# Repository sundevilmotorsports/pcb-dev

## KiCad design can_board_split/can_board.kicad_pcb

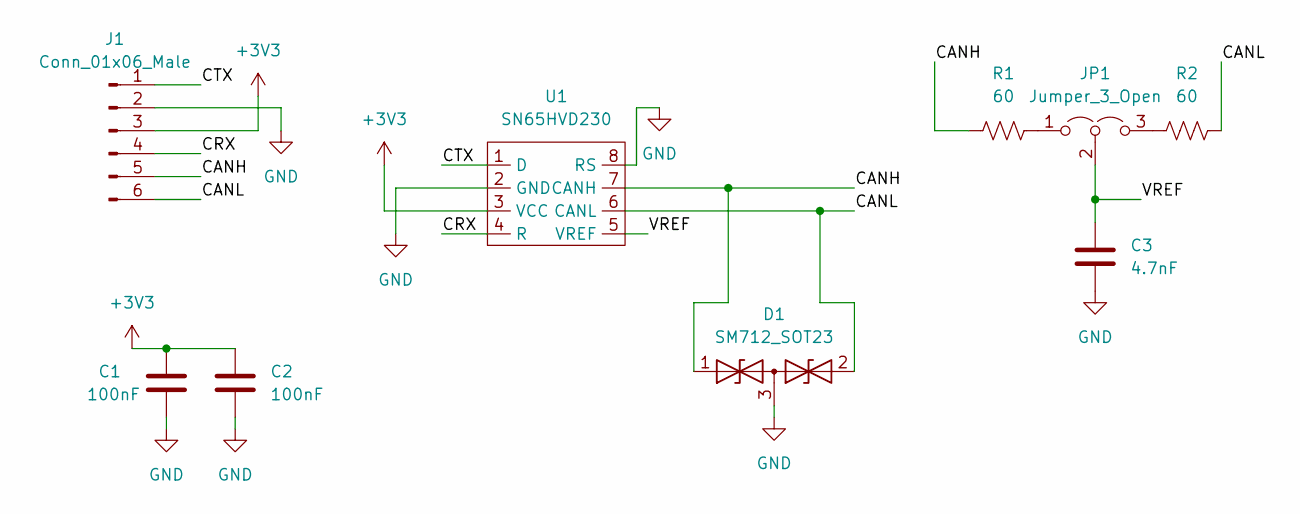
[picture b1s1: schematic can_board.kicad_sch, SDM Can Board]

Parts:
C1, C2: 100nF; CP_EIA-1608-08_AVX-J
C3: 4.7nF; CP_EIA-1608-08_AVX-J
D1: SM712_SOT23; SOT-23
J1: Conn_01x06_Male; PinHeader_1x06_P2.54mm_Vertical
JP1: Jumper_3_Open; PinHeader_1x03_P2.54mm_Vertical
R1, R2: 60; R_0603_1608Metric
U1: SN65HVD230; SOIC-8_3.9x4.9mm_P1.27mm

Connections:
+3V3: C1.1, C2.1, J1.3, U1.3 (VCC)
/CANH: D1.1 (A1), J1.5, R1.1, U1.7 (CANH)
/CANL: D1.2 (A2), J1.6, R2.2, U1.6 (CANL)
/CRX: J1.4, U1.4 (R)
/CTX: J1.1, U1.1 (D)
/VREF: C3.1, JP1.2 (C), U1.5 (VREF)
GND: C1.2, C2.2, C3.2, D1.3 (common), J1.2, U1.2 (GND), U1.8 (RS)
unnamed: JP1.1 (A), R1.2
unnamed: JP1.3 (B), R2.1

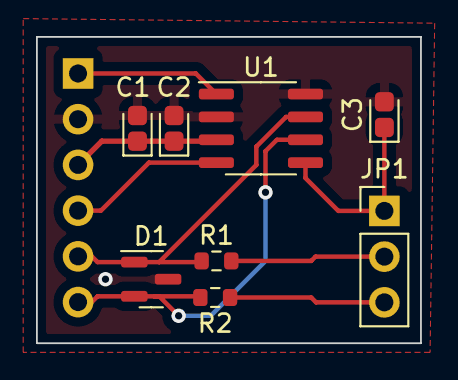
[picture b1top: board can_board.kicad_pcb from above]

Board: 2 copper layers, 21.3 x 17.0 mm, 9 parts (1 on the bottom side), 9 nets.

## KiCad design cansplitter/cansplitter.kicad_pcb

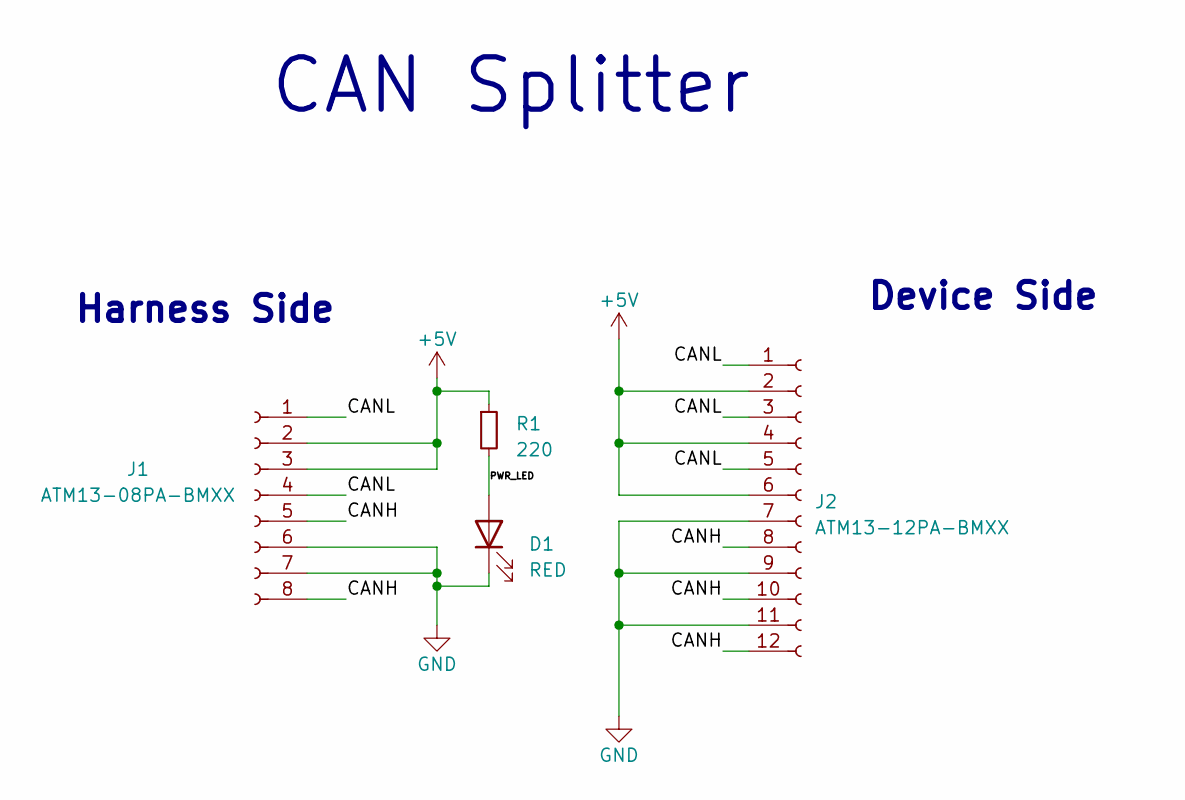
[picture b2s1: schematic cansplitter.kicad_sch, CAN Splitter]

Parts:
D1: RED; LED_1206_3216Metric
J1: ATM13-08PA-BMXX
J2: ATM13-12PA-BMXX
R1: 220; R_1206_3216Metric

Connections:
+5V: J1.2, J1.3, J2.2, J2.4, J2.6, R1.1
/CANH: J1.5, J1.8, J2.8, J2.10, J2.12
/CANL: J1.1, J1.4, J2.1, J2.3, J2.5
/PWR_LED: D1.2 (A), R1.2
GND: D1.1 (K), J1.6, J1.7, J2.7, J2.9, J2.11

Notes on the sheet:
Harness Side
Device Side
CAN Splitter

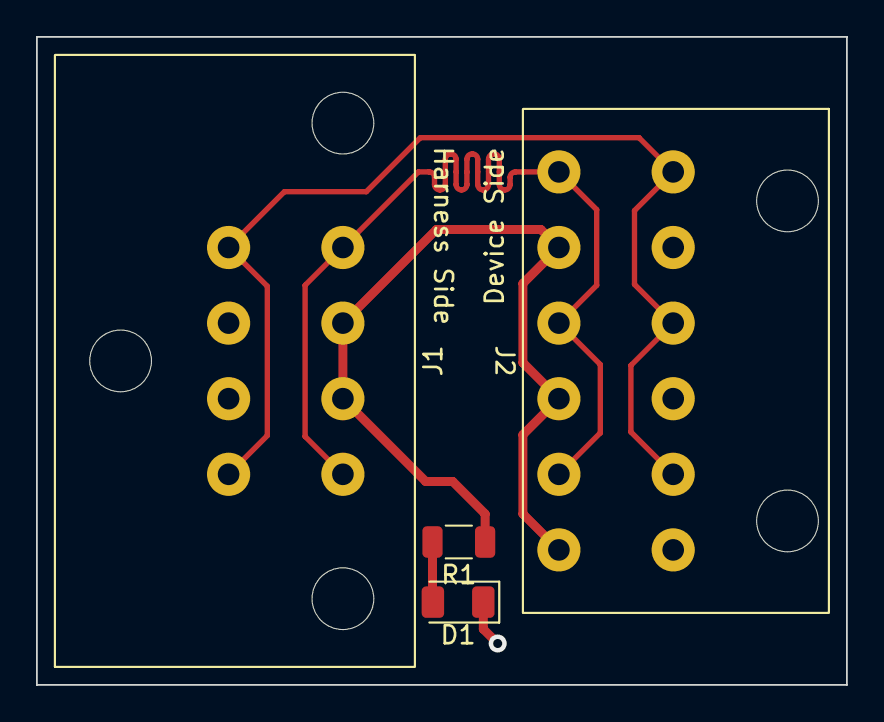
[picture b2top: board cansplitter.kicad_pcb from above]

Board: 2 copper layers, 45.0 x 36.0 mm, 4 parts (0 on the bottom side), 5 nets.

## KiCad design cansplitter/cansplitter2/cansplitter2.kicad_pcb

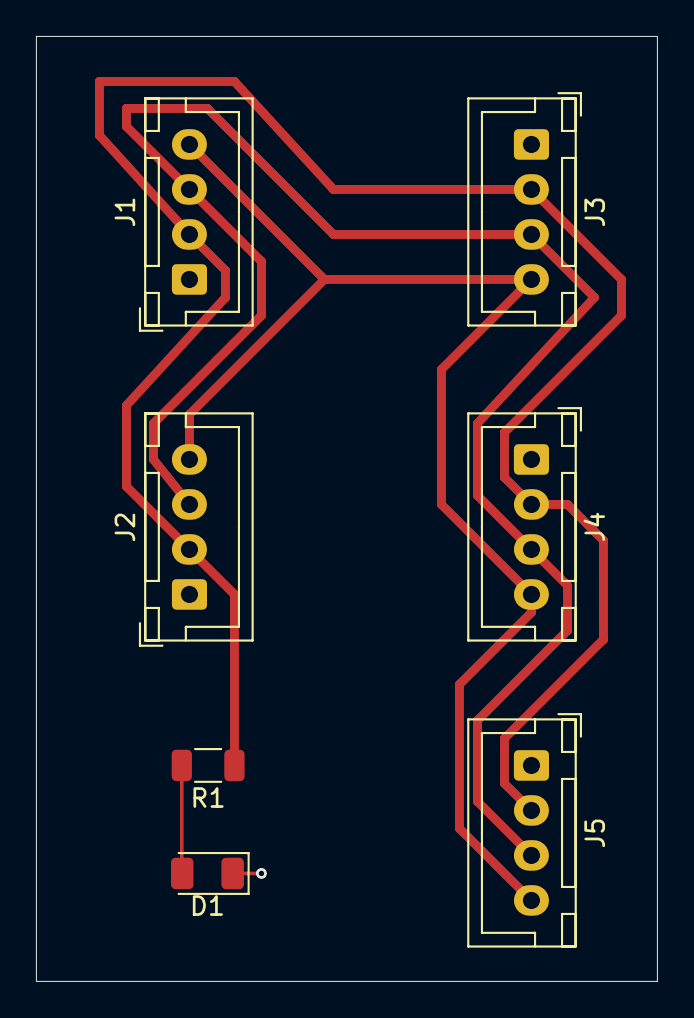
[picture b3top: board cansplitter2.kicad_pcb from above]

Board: 2 copper layers, 34.5 x 52.5 mm, 7 parts (0 on the bottom side), 5 nets.

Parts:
D1: RED; LED_1206_3216Metric
J1, J2, J3, J4, J5: JST-XH 1x4; JST_XH_B4B-XH-A_1x04_P2.50mm_Vertical
R1: 220; R_1206_3216Metric

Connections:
+5V: J1.2, J2.2, J3.2, J4.2, J5.2, R1.1
/CANH: J1.4, J2.4, J3.4, J4.4, J5.4
/CANL: J1.3, J2.3, J3.3, J4.3, J5.3
/PWR_LED: D1.2 (A), R1.2
GND: D1.1 (K), J1.1, J2.1, J3.1, J4.1, J5.1

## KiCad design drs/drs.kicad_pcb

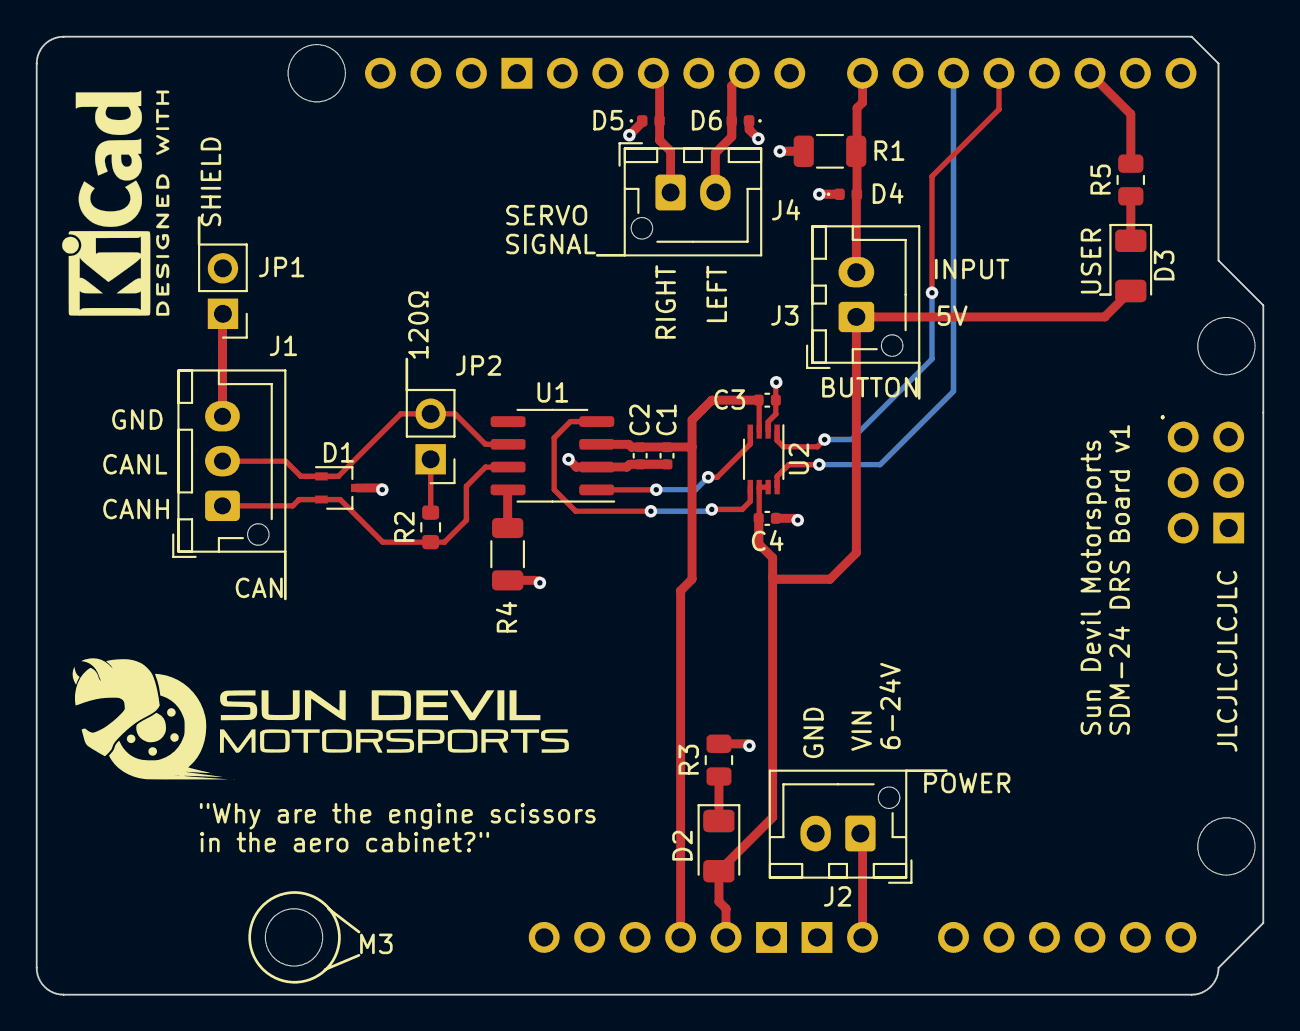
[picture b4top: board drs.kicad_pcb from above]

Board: 2 copper layers, 68.5 x 53.5 mm, 24 parts (0 on the bottom side), 19 nets.

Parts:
A1: Arduino_Uno_R4_Minima_Shield
C1, C2, C3, C4: 100nF; C_0402_1005Metric
D1: ESDCAN; SOT-323_SC-70
D2: GREEN; LED_1206_3216Metric
D3: RED; LED_1206_3216Metric
D4, D5, D6: GG040205170N2P; D_0402_1005Metric
J1: CAN; JST_XH_B3B-XH-AM_1x03_P2.50mm_Vertical
J2: POWER; JST_XH_B2B-XH-AM_1x02_P2.50mm_Vertical
J3: BUTTON; JST_XH_B2B-XH-AM_1x02_P2.50mm_Vertical
J4: SERVO; JST_XH_B2B-XH-AM_1x02_P2.50mm_Vertical
JP1: Shield; PinHeader_1x02_P2.54mm_Vertical
JP2: CAN; PinHeader_1x02_P2.54mm_Vertical
R1, R4: 10k; R_1206_3216Metric
R2: 120; R_0603_1608Metric
R3, R5: 220; R_0805_2012Metric
U1: SN65HVD230; SOIC-8_3.9x4.9mm_P1.27mm
U2: TXU0202; VSSOP-8_2.3x2mm_P0.5mm

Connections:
+3.3V: A1.3V3 (3.3V), C1.1, C2.1, C3.1, U1.3 (VCC), U2.3 (VCCA)
+5V: A1.5V1 (5V), C4.1, D2.2 (A), D3.2 (A), J3.1, U2.6 (OE), U2.7 (VCCB)
/BTN_INPUT: A1.D7, D4.2 (A2), J3.2, R1.1
/BUS_TERMINATION: JP2.1 (A), R2.2
/CANH: D1.2 (A2), J1.1, R2.1, U1.7 (CANH)
/CANL: D1.1 (A1), J1.2, JP2.2 (B), U1.6 (CANL)
/CAN_Rs: R4.1, U1.8 (Rs)
/CRX_3V3: U1.4 (R), U2.5 (A1)
/CRX_5V: A1.D5, U2.8 (B1Y)
/CTX_3V3: U1.1 (D), U2.4 (A2Y)
/CTX_5V: A1.D4, U2.1 (B2)
/PWR_LED: D2.1 (K), R3.1
/SERVO_LEFT: A1.D9, D6.2 (A2), J4.2
/SERVO_RIGHT: A1.D11, D5.2 (A2), J4.1
/SHIELD: J1.3, JP1.1 (A)
/USR_LED: A1.D2, R5.2
/USR_LED_RSTR: D3.1 (K), R5.1
GND: A1.GND1 (GND), A1.GND2 (GND), A1.GND3 (GND), C1.2, C2.2, C3.2, C4.2, D1.3 (common), D4.1 (A1), D5.1 (A1), D6.1 (A1), J2.2, JP1.2 (B), R1.2, R3.2, R4.2, U1.2 (GND), U2.2 (GND)
VCC: A1.VIN, J2.1

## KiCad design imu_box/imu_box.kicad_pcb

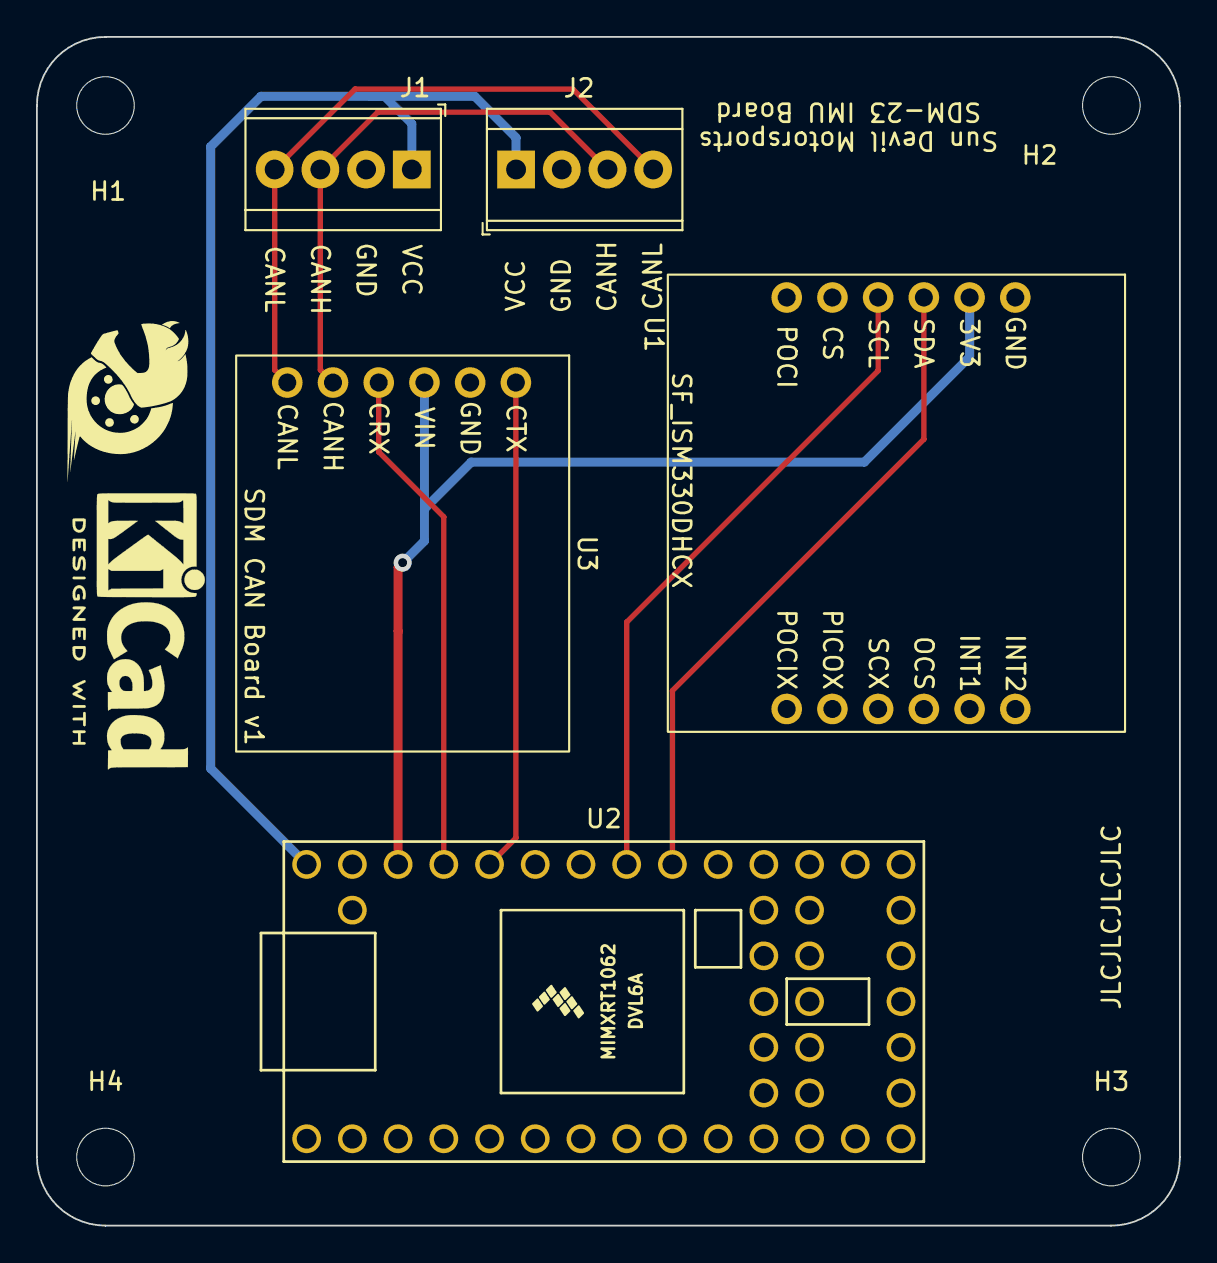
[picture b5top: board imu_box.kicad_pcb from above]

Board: 2 copper layers, 63.5 x 66.0 mm, 9 parts (0 on the bottom side), 9 nets.

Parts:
H1, H2, H3, H4: MountingHole; MountingHole_3.2mm_M3
J1, J2: CANConnection; TerminalBlock_TE_282834-4_1x04_P2.54mm_Horizontal
U1: SF_ISM330DHCX
U2: Teensy4.0; Teensy40
U3: SN65HVD230_CAN_Transceiver; SDM_CANBoard_v1

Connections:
+3V3: U1.2 (3V3), U2.31 (3V3), U3.3 (3V3)
GND: J1.2 (GND), J2.2 (GND), U1.1 (GND), U2.1 (GND), U2.32 (GND), U3.2 (GND)
unnamed: J1.3 (CANH), J2.3 (CANH), U3.5 (CANH)
unnamed: J1.4 (CANL), J2.4 (CANL), U3.6 (CANL)
unnamed: U1.3 (SDA), U2.25 (18_A4_SDA0)
unnamed: U1.4 (SCL), U2.26 (19_A5_SCL0)
unnamed: U2.29 (22_A8_CTX1), U3.1 (CTX)
unnamed: U2.30 (23_A9_CRX1_MCLK1), U3.4 (CRX)
VCC: J1.1 (VIN), J2.1 (VIN), U2.33 (VIN)

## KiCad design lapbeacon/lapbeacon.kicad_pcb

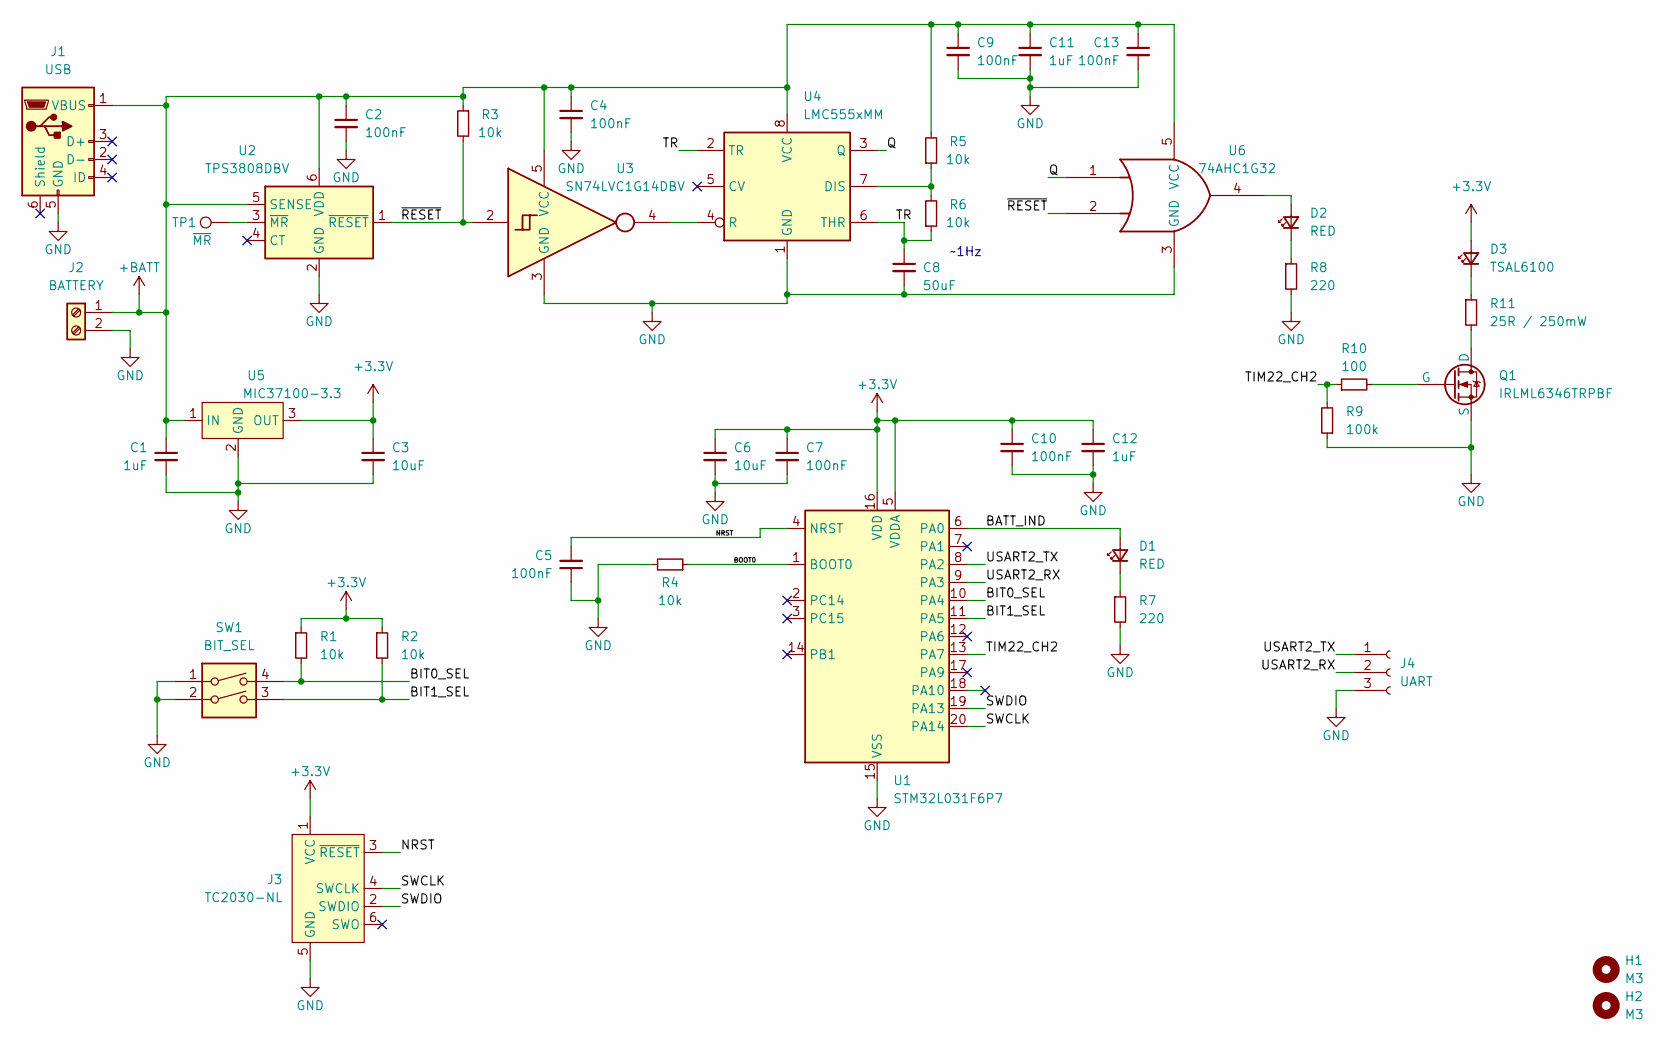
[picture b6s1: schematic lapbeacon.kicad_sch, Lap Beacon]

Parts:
C1, C11, C12: 1uF; C_0603_1608Metric
C2, C4, C5, C7, C9, C10, C13: 100nF; C_0402_1005Metric
C3, C6: 10uF; C_0805_2012Metric
C8: 50uF; C_0603_1608Metric
D1, D2: RED; LED_0603_1608Metric
D3: TSAL6100; LED_D5.0mm_IRBlack
H1, H2: M3; MountingHole_3.2mm_M3
J1: USB; USB_Micro-B_Molex-105017-0001
J2: BATTERY; TerminalBlock_TE_282834-2_1x02_P2.54mm_Horizontal
J3: TC2030-NL; Tag-Connect_TC2030-IDC-NL_2x03_P1.27mm_Vertical
J4: UART; JST_XH_B3B-XH-A_1x03_P2.50mm_Vertical
Q1: IRLML6346TRPBF; SOT-23
R1, R2: 10k; R_0805_2012Metric
R3, R5, R6: 10k; R_0402_1005Metric
R4: 10k; R_0603_1608Metric
R7, R8: 220; R_0603_1608Metric
R9: 100k; R_0805_2012Metric
R10: 100; R_0603_1608Metric
R11: 25R / 250mW; R_0603_1608Metric
SW1: BIT_SEL; 2454985-3
TP1: ~{MR}; TestPoint_Pad_1.0x1.0mm
U1: STM32L031F6P7; TSSOP-20_4.4x6.5mm_P0.65mm
U2: TPS3808DBV; SOT-23-6
U3: SN74LVC1G14DBV; SOT-23-5
U4: LMC555xMM; VSSOP-8_3.0x3.0mm_P0.65mm
U5: MIC37100-3.3; SOT-223-3_TabPin2
U6: 74AHC1G32; SOT-23-5

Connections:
+3.3V: C3.1, C6.1, C7.1, C10.1, C12.1, D3.2 (A), J3.1 (VCC), R1.1, R2.1, U1.5 (VDDA), U1.16 (VDD), U5.3 (OUT); also elsewhere on the board
+BATT: C1.1, C2.1, C4.1, C9.1, C11.1, C13.1, J1.1 (VBUS), J2.1, R3.1, R5.2, U2.5 (SENSE), U2.6 (VDD), U3.5 (VCC), U4.8 (VCC), U5.1 (IN), U6.5 (VCC)
/BATT_LED: D2.2 (A), U6.4
/BIT0_SEL: R1.2, SW1.4, U1.10 (PA4)
/BIT1_SEL: R2.2, SW1.3, U1.11 (PA5)
/BOOT0: R4.1, U1.1 (BOOT0)
/NRST: C5.2, J3.3 (~RESET), U1.4 (NRST)
/Q: U4.3 (Q), U6.1
/SWCLK: J3.4 (SWCLK), U1.20 (PA14)
/SWDIO: J3.2 (SWDIO), U1.19 (PA13)
/TIM22_CH2: R9.2, R10.1, U1.13 (PA7)
/TR: C8.1, R6.1, U4.2 (TR), U4.6 (THR)
/USART2_RX: J4.2, U1.9 (PA3)
/USART2_TX: J4.1, U1.8 (PA2)
/USER_LED: D1.2 (A), U1.6 (PA0)
/~RESET: R3.2, U2.1 (~RESET), U3.2, U6.2
GND: C1.2, C2.2, C3.2, C4.2, C5.1, C6.2, C7.2, C8.2, C9.2, C10.2, C11.2, C12.2, C13.2, J1.5 (GND), J2.2, J3.5 (GND), J4.3, Q1.3 (S), R4.2, R7.2, R8.2, R9.1, SW1.1, SW1.2, U1.15 (VSS), U2.2 (GND), U3.3 (GND), U4.1 (GND), U5.2 (GND), U6.3 (GND); also elsewhere on the board
unnamed: D1.1 (K), R7.1
unnamed: D2.1 (K), R8.1
unnamed: D3.1 (K), R11.1
unnamed: Q1.1 (D), R11.2
unnamed: Q1.2 (G), R10.2
unnamed: TP1.1, U2.3 (~MR)
unnamed: R5.1, R6.2, U4.7 (DIS)
unnamed: U3.4, U4.4 (R)

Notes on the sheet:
~1Hz

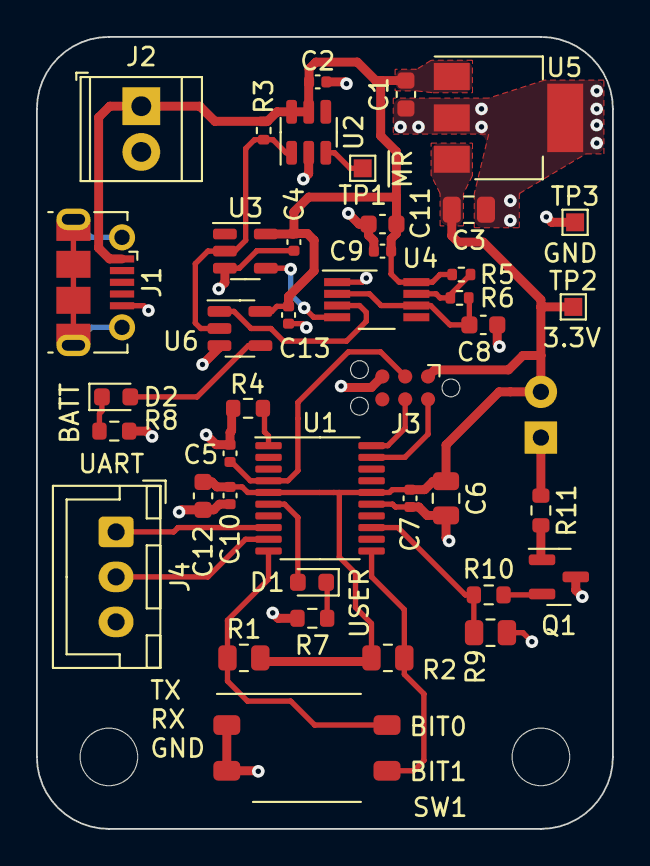
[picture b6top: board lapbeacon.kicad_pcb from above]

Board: 2 copper layers, 32.0 x 44.0 mm, 44 parts (1 on the bottom side), 25 nets.

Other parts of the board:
TP2: 3.3V; TestPoint_Pad_1.0x1.0mm
TP3: GND; TestPoint_Pad_1.0x1.0mm

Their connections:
+3.3V: TP2.1; also elsewhere on the board
GND: TP3.1; also elsewhere on the board
